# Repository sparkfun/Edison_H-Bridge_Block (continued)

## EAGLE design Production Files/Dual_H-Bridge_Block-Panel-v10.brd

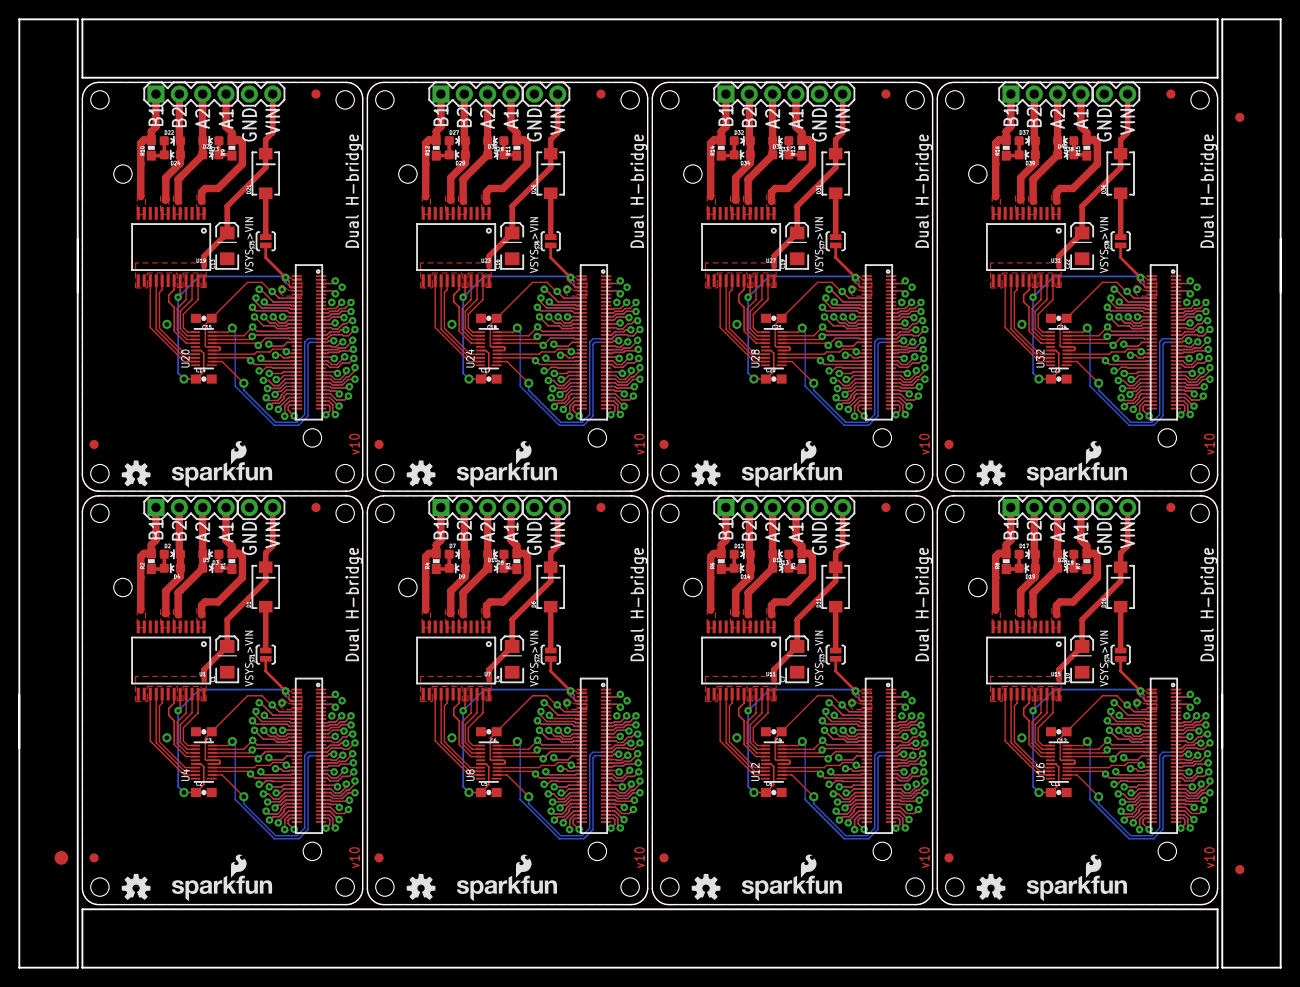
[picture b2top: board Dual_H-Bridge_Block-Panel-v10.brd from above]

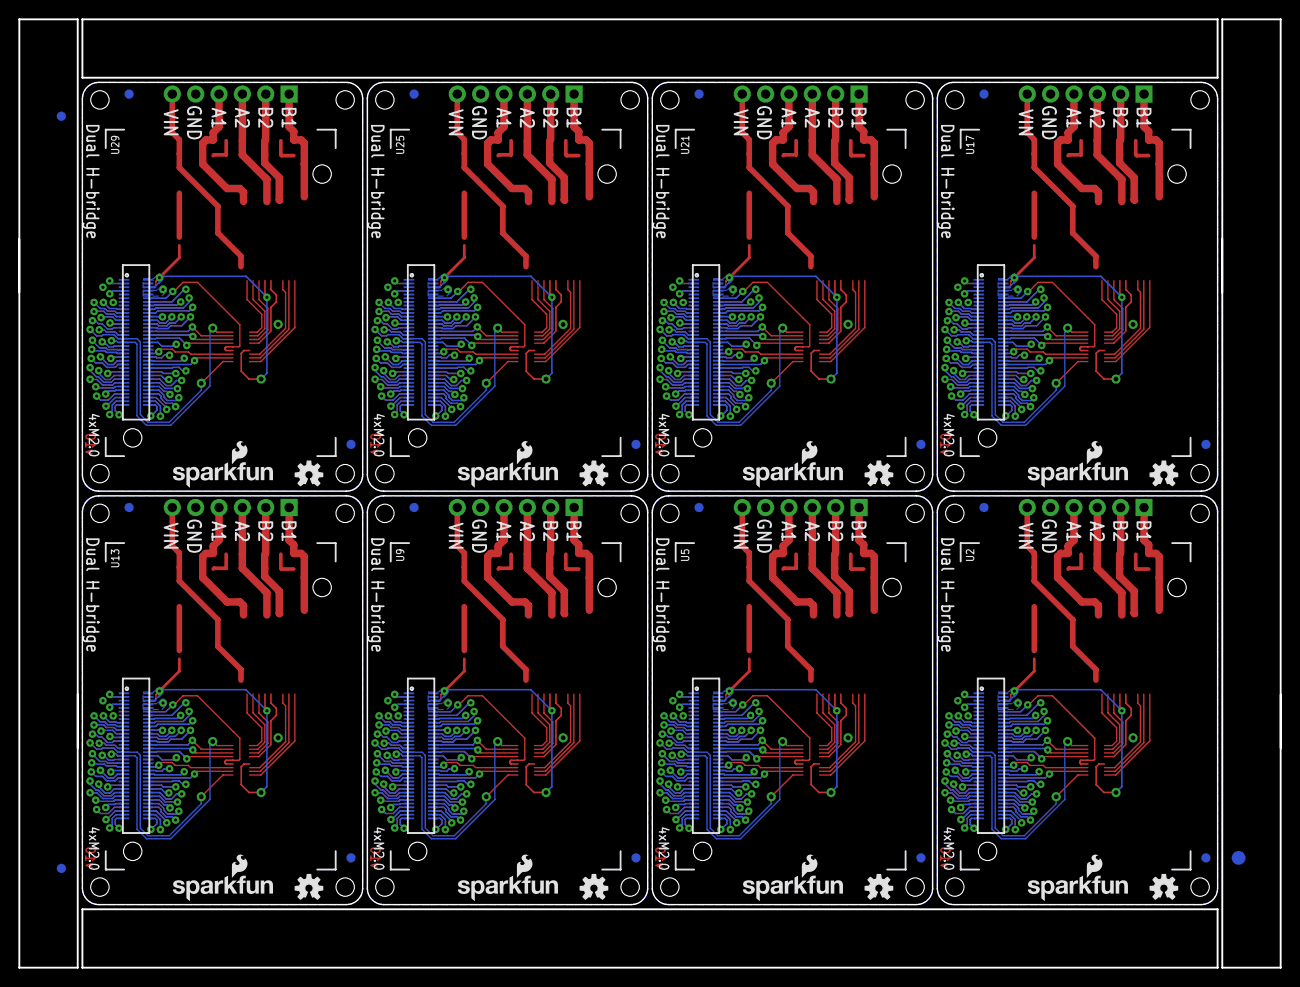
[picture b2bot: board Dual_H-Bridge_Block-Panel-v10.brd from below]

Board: 2 copper layers, 137.2 x 103.1 mm, 206 parts (51 on the bottom side), 584 nets.

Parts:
C1, C4, C7, C10, C13, C16, C19, C22: 10uF; EIA3216
C2, C3, C5, C6, C8, C9, C11, C12, C14, C15, C17, C18, C20, C21, C23, C24: 0.1uF; 0603-CAP
D1, D6, D11, D16, D21, D26, D31, D36: MBRA140; SMA-DIODE
D2, D3, D7, D8, D12, D13, D17, D18, D22, D23, D27, D28, D32, D33, D37, D38: GREEN; LED-0603
D4, D5, D9, D10, D14, D15, D19, D20, D24, D25, D29, D30, D34, D35, D39, D40: RED; LED-0603
E$1, E$2: FIDUCIAL-1.5X3
E$3, E$4, E$5, E$6: FIDUCIAL-1X2
FID1, FID2, FID3, FID4, FID5, FID6, FID7, FID8, FID9, FID10, FID11, FID12, FID13, FID14, FID15, FID16, FID17, FID18, FID19, FID20, FID21, FID22, FID23, FID24, FID25, FID26, FID27, FID28, FID29, FID30, FID31, FID32: FIDUCIAL1X2; FIDUCIAL-1X2
JP1, JP3, JP5, JP7, JP9, JP11, JP13, JP15: 1X04
JP2, JP4, JP6, JP8, JP10, JP12, JP14, JP16: M02PTH; 1X02
LOGO1, LOGO2, LOGO5, LOGO7, LOGO9, LOGO11, LOGO13, LOGO15, LOGO17, LOGO19, LOGO21, LOGO23, LOGO25, LOGO27, LOGO29, LOGO31: OSHW-LOGOS; OSHW-LOGO-S
LOGO3, LOGO4, LOGO6, LOGO8, LOGO10, LOGO12, LOGO14, LOGO16, LOGO18, LOGO20, LOGO22, LOGO24, LOGO26, LOGO28, LOGO30, LOGO32: SFE_LOGO_NAME_FLAME.1_INCH; SFE_LOGO_NAME_FLAME_.1
R1, R2, R3, R4, R5, R6, R7, R8, R9, R10, R11, R12, R13, R14, R15, R16: 680; 0603-RES
SJ1, SJ2, SJ3, SJ4, SJ5, SJ6, SJ7, SJ8: VSYS ENABLE; PAD-JUMPER-2-NO_YES_SILK
U1, U7, U11, U15, U19, U23, U27, U31: TB6612FNG; SSOP24
U2, U5, U9, U13, U17, U21, U25, U29: EDISON_CONNECTOR_FULLMOUNTING_HOLES; EDISON_DAUGHTER
U3, U6, U10, U14, U18, U22, U26, U30: EDISON_CONNECTOR_FULLHEADER; DF40C-70DP-0.4(51)
U4, U8, U12, U16, U20, U24, U28, U32: TXB0108; UFDFN-20

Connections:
1.8V: C3.1, U2.12, U3.12, U4.5, U4.6
1.8V1: C6.1, U5.12, U6.12, U8.5, U8.6
1.8V2: C9.1, U9.12, U10.12, U12.5, U12.6
1.8V3: C12.1, U13.12, U14.12, U16.5, U16.6
1.8V4: C15.1, U17.12, U18.12, U20.5, U20.6
1.8V5: C18.1, U21.12, U22.12, U24.5, U24.6
1.8V6: C21.1, U25.12, U26.12, U28.5, U28.6
1.8V7: C24.1, U29.12, U30.12, U32.5, U32.6
3.3V: U2.8, U2.10, U3.8, U3.10
3.3V1: U5.8, U5.10, U6.8, U6.10
3.3V2: U9.8, U9.10, U10.8, U10.10
3.3V3: U13.8, U13.10, U14.8, U14.10
3.3V4: U17.8, U17.10, U18.8, U18.10
3.3V5: U21.8, U21.10, U22.8, U22.10
3.3V6: U25.8, U25.10, U26.8, U26.10
3.3V7: U29.8, U29.10, U30.8, U30.10
A1: JP1.4, R1.2, U1.1, U1.2
A2: D3.C, D5.A, JP1.3, U1.5, U1.6
A3: D8.C, D10.A, JP3.3, U7.5, U7.6
A4: JP3.4, R3.2, U7.1, U7.2
A5: D13.C, D15.A, JP5.3, U11.5, U11.6
A6: JP5.4, R5.2, U11.1, U11.2
A7: D18.C, D20.A, JP7.3, U15.5, U15.6
A8: JP7.4, R7.2, U15.1, U15.2
A9: D23.C, D25.A, JP9.3, U19.5, U19.6
A10: JP9.4, R9.2, U19.1, U19.2
A11: D28.C, D30.A, JP11.3, U23.5, U23.6
A12: JP11.4, R11.2, U23.1, U23.2
A13: D33.C, D35.A, JP13.3, U27.5, U27.6
A14: JP13.4, R13.2, U27.1, U27.2
A15: D38.C, D40.A, JP15.3, U31.5, U31.6
A16: JP15.4, R15.2, U31.1, U31.2
B1: JP1.1, R2.2, U1.11, U1.12
B2: D2.C, D4.A, JP1.2, U1.7, U1.8
B3: JP3.1, R4.2, U7.11, U7.12
B4: D7.C, D9.A, JP3.2, U7.7, U7.8
B5: JP5.1, R6.2, U11.11, U11.12
B6: D12.C, D14.A, JP5.2, U11.7, U11.8
B7: JP7.1, R8.2, U15.11, U15.12
B8: D17.C, D19.A, JP7.2, U15.7, U15.8
B9: JP9.1, R10.2, U19.11, U19.12
B10: D22.C, D24.A, JP9.2, U19.7, U19.8
B11: JP11.1, R12.2, U23.11, U23.12
B12: D27.C, D29.A, JP11.2, U23.7, U23.8
B13: JP13.1, R14.2, U27.11, U27.12
B14: D32.C, D34.A, JP13.2, U27.7, U27.8
B15: JP15.1, R16.2, U31.11, U31.12
B16: D37.C, D39.A, JP15.2, U31.7, U31.8
DCIN: U2.14, U3.14
DCIN1: U5.14, U6.14
DCIN2: U9.14, U10.14
DCIN3: U13.14, U14.14
DCIN4: U17.14, U18.14
DCIN5: U21.14, U22.14
DCIN6: U25.14, U26.14
DCIN7: U29.14, U30.14
FAULT: U2.19, U3.19
FAULT1: U5.19, U6.19
FAULT2: U9.19, U10.19
FAULT3: U13.19, U14.19
FAULT4: U17.19, U18.19
FAULT5: U21.19, U22.19
FAULT6: U25.19, U26.19
FAULT7: U29.19, U30.19
FW_RCVR: U2.69, U3.69
FW_RCVR1: U5.69, U6.69
FW_RCVR2: U9.69, U10.69
FW_RCVR3: U13.69, U14.69
FW_RCVR4: U17.69, U18.69
FW_RCVR5: U21.69, U22.69
FW_RCVR6: U25.69, U26.69
FW_RCVR7: U29.69, U30.69
GND: C1.C, C2.2, C3.2, JP2.1, U1.3, U1.4, U1.9, U1.10, U1.18, U2.1, U2.5, U2.9, U2.11, U2.13, U2.15, U3.1, U3.5, U3.9, U3.11, U3.13, U3.15, U4.15
GND1: C4.C, C5.2, C6.2, JP4.1, U5.1, U5.5, U5.9, U5.11, U5.13, U5.15, U6.1, U6.5, U6.9, U6.11, U6.13, U6.15, U7.3, U7.4, U7.9, U7.10, U7.18, U8.15
GND2: C7.C, C8.2, C9.2, JP6.1, U9.1, U9.5, U9.9, U9.11, U9.13, U9.15, U10.1, U10.5, U10.9, U10.11, U10.13, U10.15, U11.3, U11.4, U11.9, U11.10, U11.18, U12.15
GND3: C10.C, C11.2, C12.2, JP8.1, U13.1, U13.5, U13.9, U13.11, U13.13, U13.15, U14.1, U14.5, U14.9, U14.11, U14.13, U14.15, U15.3, U15.4, U15.9, U15.10, U15.18, U16.15
GND4: C13.C, C14.2, C15.2, JP10.1, U17.1, U17.5, U17.9, U17.11, U17.13, U17.15, U18.1, U18.5, U18.9, U18.11, U18.13, U18.15, U19.3, U19.4, U19.9, U19.10, U19.18, U20.15
GND5: C16.C, C17.2, C18.2, JP12.1, U21.1, U21.5, U21.9, U21.11, U21.13, U21.15, U22.1, U22.5, U22.9, U22.11, U22.13, U22.15, U23.3, U23.4, U23.9, U23.10, U23.18, U24.15
GND6: C19.C, C20.2, C21.2, JP14.1, U25.1, U25.5, U25.9, U25.11, U25.13, U25.15, U26.1, U26.5, U26.9, U26.11, U26.13, U26.15, U27.3, U27.4, U27.9, U27.10, U27.18, U28.15
GND7: C22.C, C23.2, C24.2, JP16.1, U29.1, U29.5, U29.9, U29.11, U29.13, U29.15, U30.1, U30.5, U30.9, U30.11, U30.13, U30.15, U31.3, U31.4, U31.9, U31.10, U31.18, U32.15
GP1: U5.48, U6.48, U8.3
GP2: U5.42, U6.42, U8.4
GP3: U5.34, U6.34, U8.7
GP4: U5.32, U6.32, U8.8
GP5: U5.30, U6.30, U8.9
GP6: U5.28, U6.28
GP7: U5.26, U6.26
GP8: U5.25, U6.25
GP9: U5.24, U6.24
GP10: U9.48, U10.48, U12.3
GP11: U9.42, U10.42, U12.4
GP12: U9.34, U10.34, U12.7
GP12_PWM0: U2.35, U3.35, U4.10
GP12_PWM1: U5.35, U6.35, U8.10
GP12_PWM2: U9.35, U10.35, U12.10
GP12_PWM3: U13.35, U14.35, U16.10
GP12_PWM4: U17.35, U18.35, U20.10
GP12_PWM5: U21.35, U22.35, U24.10
GP12_PWM6: U25.35, U26.35, U28.10
GP12_PWM7: U29.35, U30.35, U32.10
GP13: U9.32, U10.32, U12.8
GP13_PWM1: U2.33, U3.33, U4.2
GP13_PWM2: U5.33, U6.33, U8.2
GP13_PWM3: U9.33, U10.33, U12.2
GP13_PWM4: U13.33, U14.33, U16.2
GP13_PWM5: U17.33, U18.33, U20.2
GP13_PWM6: U21.33, U22.33, U24.2
GP13_PWM7: U25.33, U26.33, U28.2
GP13_PWM8: U29.33, U30.33, U32.2
GP14: U2.48, U3.48, U4.3
GP15: U2.42, U3.42, U4.4
GP16: U9.30, U10.30, U12.9
GP17: U9.28, U10.28
GP18: U9.26, U10.26
GP19: U9.25, U10.25
GP19_I2C_1_SCL: U2.41, U3.41
GP19_I2C_1_SCL1: U5.41, U6.41
GP19_I2C_1_SCL2: U9.41, U10.41
GP19_I2C_1_SCL3: U13.41, U14.41
GP19_I2C_1_SCL4: U17.41, U18.41
GP19_I2C_1_SCL5: U21.41, U22.41
GP19_I2C_1_SCL6: U25.41, U26.41
GP19_I2C_1_SCL7: U29.41, U30.41
GP20: U9.24, U10.24
GP20_I2C_1_SDA: U2.43, U3.43
GP20_I2C_1_SDA1: U5.43, U6.43
GP20_I2C_1_SDA2: U9.43, U10.43
GP20_I2C_1_SDA3: U13.43, U14.43
GP20_I2C_1_SDA4: U17.43, U18.43
GP20_I2C_1_SDA5: U21.43, U22.43
GP20_I2C_1_SDA6: U25.43, U26.43
GP20_I2C_1_SDA7: U29.43, U30.43
GP21: U13.48, U14.48, U16.3
GP22: U13.42, U14.42, U16.4
GP23: U13.34, U14.34, U16.7
GP24: U13.32, U14.32, U16.8
GP25: U13.30, U14.30, U16.9
GP26: U13.28, U14.28
GP27: U13.26, U14.26
GP27_I2C_6_SCL: U2.45, U3.45
GP27_I2C_6_SCL1: U5.45, U6.45
GP27_I2C_6_SCL2: U9.45, U10.45
GP27_I2C_6_SCL3: U13.45, U14.45
GP27_I2C_6_SCL4: U17.45, U18.45
GP27_I2C_6_SCL5: U21.45, U22.45
GP27_I2C_6_SCL6: U25.45, U26.45
GP27_I2C_6_SCL7: U29.45, U30.45
GP28: U13.25, U14.25
GP28_I2C_6_SDA: U2.47, U3.47
GP28_I2C_6_SDA1: U5.47, U6.47
GP28_I2C_6_SDA2: U9.47, U10.47
GP28_I2C_6_SDA3: U13.47, U14.47
GP28_I2C_6_SDA4: U17.47, U18.47
GP28_I2C_6_SDA5: U21.47, U22.47
GP28_I2C_6_SDA6: U25.47, U26.47
GP28_I2C_6_SDA7: U29.47, U30.47
GP29: U13.24, U14.24
GP30: U17.48, U18.48, U20.3
GP31: U17.42, U18.42, U20.4
GP32: U17.34, U18.34, U20.7
GP33: U17.32, U18.32, U20.8
GP34: U17.30, U18.30, U20.9
GP35: U17.28, U18.28
GP36: U17.26, U18.26
GP37: U17.25, U18.25
GP38: U17.24, U18.24
GP39: U21.48, U22.48, U24.3
GP40: U21.42, U22.42, U24.4
GP40_I2S_2_CLK: U2.52, U3.52
GP40_I2S_2_CLK1: U5.52, U6.52
GP40_I2S_2_CLK2: U9.52, U10.52
GP40_I2S_2_CLK3: U13.52, U14.52
GP40_I2S_2_CLK4: U17.52, U18.52
GP40_I2S_2_CLK5: U21.52, U22.52
GP40_I2S_2_CLK6: U25.52, U26.52
GP40_I2S_2_CLK7: U29.52, U30.52
GP41: U21.34, U22.34, U24.7
GP41_I2S_2_FS: U2.54, U3.54
GP41_I2S_2_FS1: U5.54, U6.54
GP41_I2S_2_FS2: U9.54, U10.54
GP41_I2S_2_FS3: U13.54, U14.54
GP41_I2S_2_FS4: U17.54, U18.54
GP41_I2S_2_FS5: U21.54, U22.54
GP41_I2S_2_FS6: U25.54, U26.54
GP41_I2S_2_FS7: U29.54, U30.54
GP42: U21.32, U22.32, U24.8
GP42_I2S_2_RXD: U2.50, U3.50
GP42_I2S_2_RXD1: U5.50, U6.50
GP42_I2S_2_RXD2: U9.50, U10.50
GP42_I2S_2_RXD3: U13.50, U14.50
GP42_I2S_2_RXD4: U17.50, U18.50
GP42_I2S_2_RXD5: U21.50, U22.50
GP42_I2S_2_RXD6: U25.50, U26.50
GP42_I2S_2_RXD7: U29.50, U30.50
GP43: U21.30, U22.30, U24.9
GP43_I2S_2_TXD: U2.56, U3.56
GP43_I2S_2_TXD1: U5.56, U6.56
GP43_I2S_2_TXD2: U9.56, U10.56
GP43_I2S_2_TXD3: U13.56, U14.56
GP43_I2S_2_TXD4: U17.56, U18.56
GP43_I2S_2_TXD5: U21.56, U22.56
GP43_I2S_2_TXD6: U25.56, U26.56
GP43_I2S_2_TXD7: U29.56, U30.56
GP44: U2.24, U3.24
GP45: U2.26, U3.26
GP46: U2.28, U3.28
GP47: U2.30, U3.30, U4.9
GP48: U2.32, U3.32, U4.8
GP49: U2.34, U3.34, U4.7
GP50: U21.28, U22.28
GP51: U21.26, U22.26
GP52: U21.25, U22.25
GP53: U21.24, U22.24
GP54: U25.48, U26.48, U28.3
GP55: U25.42, U26.42, U28.4
GP56: U25.34, U26.34, U28.7
GP57: U25.32, U26.32, U28.8
GP58: U25.30, U26.30, U28.9
GP59: U25.28, U26.28
GP60: U25.26, U26.26
GP61: U25.25, U26.25
GP62: U25.24, U26.24
GP63: U29.48, U30.48, U32.3
GP64: U29.42, U30.42, U32.4
GP65: U29.34, U30.34, U32.7
GP66: U29.32, U30.32, U32.8
GP67: U29.30, U30.30, U32.9
GP68: U29.28, U30.28
GP69: U29.26, U30.26
GP70: U29.25, U30.25
GP71: U29.24, U30.24
GP77_SD_0_CD#: U2.60, U3.60
GP77_SD_0_CD#1: U5.60, U6.60
GP77_SD_0_CD#2: U9.60, U10.60
GP77_SD_0_CD#3: U13.60, U14.60
GP77_SD_0_CD#4: U17.60, U18.60
GP77_SD_0_CD#5: U21.60, U22.60
GP77_SD_0_CD#6: U25.60, U26.60
GP77_SD_0_CD#7: U29.60, U30.60
GP78_SD_0_CLK: U2.58, U3.58
GP78_SD_0_CLK1: U5.58, U6.58
GP78_SD_0_CLK2: U9.58, U10.58
GP78_SD_0_CLK3: U13.58, U14.58
GP78_SD_0_CLK4: U17.58, U18.58
GP78_SD_0_CLK5: U21.58, U22.58
GP78_SD_0_CLK6: U25.58, U26.58
GP78_SD_0_CLK7: U29.58, U30.58
GP79_SD_0_CMD: U2.62, U3.62
GP79_SD_0_CMD1: U5.62, U6.62
GP79_SD_0_CMD2: U9.62, U10.62
GP79_SD_0_CMD3: U13.62, U14.62
GP79_SD_0_CMD4: U17.62, U18.62
GP79_SD_0_CMD5: U21.62, U22.62
GP79_SD_0_CMD6: U25.62, U26.62
GP79_SD_0_CMD7: U29.62, U30.62
GP80_SD_0_DAT0: U2.66, U3.66
GP80_SD_0_DAT1: U5.66, U6.66
GP80_SD_0_DAT2: U9.66, U10.66
GP80_SD_0_DAT3: U13.66, U14.66
GP80_SD_0_DAT4: U17.66, U18.66
GP80_SD_0_DAT5: U21.66, U22.66
GP80_SD_0_DAT6: U25.66, U26.66
GP80_SD_0_DAT7: U29.66, U30.66
GP81_SD_0_DAT1: U2.70, U3.70
GP81_SD_0_DAT2: U5.70, U6.70
GP81_SD_0_DAT3: U9.70, U10.70
GP81_SD_0_DAT4: U13.70, U14.70
GP81_SD_0_DAT5: U17.70, U18.70
GP81_SD_0_DAT6: U21.70, U22.70
GP81_SD_0_DAT7: U25.70, U26.70
GP81_SD_0_DAT8: U29.70, U30.70
GP82_SD_0_DAT1: U5.64, U6.64
GP82_SD_0_DAT2: U2.64, U3.64
GP82_SD_0_DAT3: U9.64, U10.64
GP82_SD_0_DAT4: U13.64, U14.64
GP82_SD_0_DAT5: U17.64, U18.64
GP82_SD_0_DAT6: U21.64, U22.64
GP82_SD_0_DAT7: U25.64, U26.64
GP82_SD_0_DAT8: U29.64, U30.64
GP83_SD_0_DAT1: U5.68, U6.68
GP83_SD_0_DAT2: U9.68, U10.68
GP83_SD_0_DAT3: U2.68, U3.68
GP83_SD_0_DAT4: U13.68, U14.68
GP83_SD_0_DAT5: U17.68, U18.68
GP83_SD_0_DAT6: U21.68, U22.68
GP83_SD_0_DAT7: U25.68, U26.68
GP83_SD_0_DAT8: U29.68, U30.68
GP84_SD_CLK_FB: U2.44, U3.44
GP84_SD_CLK_FB1: U5.44, U6.44
GP84_SD_CLK_FB2: U9.44, U10.44
GP84_SD_CLK_FB3: U13.44, U14.44
GP84_SD_CLK_FB4: U17.44, U18.44
GP84_SD_CLK_FB5: U21.44, U22.44
GP84_SD_CLK_FB6: U25.44, U26.44
GP84_SD_CLK_FB7: U29.44, U30.44
GP109_SPI_2_CLK: U2.55, U3.55
GP109_SPI_2_CLK1: U5.55, U6.55
GP109_SPI_2_CLK2: U9.55, U10.55
GP109_SPI_2_CLK3: U13.55, U14.55
GP109_SPI_2_CLK4: U17.55, U18.55
GP109_SPI_2_CLK5: U21.55, U22.55
GP109_SPI_2_CLK6: U25.55, U26.55
GP109_SPI_2_CLK7: U29.55, U30.55
GP110_SPI_2_FS0: U2.53, U3.53
GP110_SPI_2_FS1: U5.53, U6.53
GP110_SPI_2_FS2: U9.53, U10.53
GP110_SPI_2_FS3: U13.53, U14.53
GP110_SPI_2_FS4: U17.53, U18.53
GP110_SPI_2_FS5: U21.53, U22.53
GP110_SPI_2_FS6: U25.53, U26.53
GP110_SPI_2_FS7: U29.53, U30.53
GP111_SPI_2_FS1: U2.51, U3.51
GP111_SPI_2_FS2: U5.51, U6.51
GP111_SPI_2_FS3: U9.51, U10.51
GP111_SPI_2_FS4: U13.51, U14.51
GP111_SPI_2_FS5: U17.51, U18.51
GP111_SPI_2_FS6: U21.51, U22.51
GP111_SPI_2_FS7: U25.51, U26.51
GP111_SPI_2_FS8: U29.51, U30.51
GP114_SPI_2_RXD: U2.59, U3.59
GP114_SPI_2_RXD1: U5.59, U6.59
GP114_SPI_2_RXD2: U9.59, U10.59
GP114_SPI_2_RXD3: U13.59, U14.59
GP114_SPI_2_RXD4: U17.59, U18.59
GP114_SPI_2_RXD5: U21.59, U22.59
GP114_SPI_2_RXD6: U25.59, U26.59
GP114_SPI_2_RXD7: U29.59, U30.59
GP115_SPI_2_TXD: U2.57, U3.57
GP115_SPI_2_TXD1: U5.57, U6.57
GP115_SPI_2_TXD2: U9.57, U10.57
GP115_SPI_2_TXD3: U13.57, U14.57
GP115_SPI_2_TXD4: U17.57, U18.57
GP115_SPI_2_TXD5: U21.57, U22.57
GP115_SPI_2_TXD6: U25.57, U26.57
GP115_SPI_2_TXD7: U29.57, U30.57
GP128_UART_1_CTS: U2.65, U3.65
GP128_UART_1_CTS1: U5.65, U6.65
GP128_UART_1_CTS2: U9.65, U10.65
GP128_UART_1_CTS3: U13.65, U14.65
GP128_UART_1_CTS4: U17.65, U18.65
GP128_UART_1_CTS5: U21.65, U22.65
GP128_UART_1_CTS6: U25.65, U26.65
GP128_UART_1_CTS7: U29.65, U30.65
GP129_UART_1_RTS: U2.63, U3.63
GP129_UART_1_RTS1: U5.63, U6.63
GP129_UART_1_RTS2: U9.63, U10.63
GP129_UART_1_RTS3: U13.63, U14.63
GP129_UART_1_RTS4: U17.63, U18.63
GP129_UART_1_RTS5: U21.63, U22.63
GP129_UART_1_RTS6: U25.63, U26.63
GP129_UART_1_RTS7: U29.63, U30.63
GP130_UART_1_RX: U2.61, U3.61
GP130_UART_1_RX1: U5.61, U6.61
GP130_UART_1_RX2: U9.61, U10.61
GP130_UART_1_RX3: U13.61, U14.61
GP130_UART_1_RX4: U17.61, U18.61
GP130_UART_1_RX5: U21.61, U22.61
GP130_UART_1_RX6: U25.61, U26.61
GP130_UART_1_RX7: U29.61, U30.61
GP131_UART_1_TX: U2.46, U3.46
GP131_UART_1_TX1: U5.46, U6.46
GP131_UART_1_TX2: U9.46, U10.46
GP131_UART_1_TX3: U13.46, U14.46
GP131_UART_1_TX4: U17.46, U18.46
GP131_UART_1_TX5: U21.46, U22.46
GP131_UART_1_TX6: U25.46, U26.46
GP131_UART_1_TX7: U29.46, U30.46
GP134_UART_2_RX: U2.22, U3.22
GP134_UART_2_RX1: U5.22, U6.22
GP134_UART_2_RX2: U9.22, U10.22
GP134_UART_2_RX3: U13.22, U14.22
GP134_UART_2_RX4: U17.22, U18.22
GP134_UART_2_RX5: U21.22, U22.22
GP134_UART_2_RX6: U25.22, U26.22
GP134_UART_2_RX7: U29.22, U30.22
GP135_UART_2_TX: U2.27, U3.27
GP135_UART_2_TX1: U5.27, U6.27
GP135_UART_2_TX2: U9.27, U10.27
GP135_UART_2_TX3: U13.27, U14.27
GP135_UART_2_TX4: U17.27, U18.27
GP135_UART_2_TX5: U21.27, U22.27
GP135_UART_2_TX6: U25.27, U26.27
GP135_UART_2_TX7: U29.27, U30.27
GP165: U2.25, U3.25
GP182_PWM1: U5.37, U6.37
GP182_PWM2: U2.37, U3.37
GP182_PWM3: U9.37, U10.37
GP182_PWM4: U13.37, U14.37
GP182_PWM5: U17.37, U18.37
GP182_PWM6: U21.37, U22.37
GP182_PWM7: U25.37, U26.37
GP182_PWM8: U29.37, U30.37
GP183_PWM1: U5.39, U6.39
GP183_PWM2: U9.39, U10.39
GP183_PWM3: U2.39, U3.39
GP183_PWM4: U13.39, U14.39
GP183_PWM5: U17.39, U18.39
GP183_PWM6: U21.39, U22.39
GP183_PWM7: U25.39, U26.39
GP183_PWM8: U29.39, U30.39
MSIC_SLP_CLK: U2.7, U3.7
MSIC_SLP_CLK1: U5.7, U6.7
MSIC_SLP_CLK2: U9.7, U10.7
MSIC_SLP_CLK3: U13.7, U14.7
MSIC_SLP_CLK4: U17.7, U18.7
MSIC_SLP_CLK5: U21.7, U22.7
MSIC_SLP_CLK6: U25.7, U26.7
MSIC_SLP_CLK7: U29.7, U30.7
unnamed: D1.A, SJ1.2
unnamed: D2.A, D4.C, R2.1
unnamed: U1.15, U4.19
unnamed: U1.23, U4.11
unnamed: D3.A, D5.C, R1.1
unnamed: U7.19, U8.14
unnamed: U7.17, U8.17
unnamed: U7.16, U8.18
unnamed: U7.21, U8.13
unnamed: U1.19, U4.14
unnamed: U1.17, U4.17
unnamed: U1.16, U4.18
unnamed: U7.22, U8.12
unnamed: U1.21, U4.13
unnamed: U1.22, U4.12
unnamed: U7.15, U8.19
unnamed: U7.23, U8.11
unnamed: D6.A, SJ2.2
unnamed: D7.A, D9.C, R4.1
unnamed: D8.A, D10.C, R3.1
unnamed: U11.19, U12.14
unnamed: U11.17, U12.17
unnamed: U11.16, U12.18
unnamed: U11.21, U12.13
unnamed: U11.22, U12.12
unnamed: U11.15, U12.19
unnamed: U11.23, U12.11
unnamed: D11.A, SJ3.2
unnamed: D12.A, D14.C, R6.1
unnamed: D13.A, D15.C, R5.1
unnamed: U15.19, U16.14
unnamed: U15.17, U16.17
unnamed: U15.16, U16.18
unnamed: U15.21, U16.13
unnamed: U15.22, U16.12
unnamed: U15.15, U16.19
unnamed: U15.23, U16.11
unnamed: D16.A, SJ4.2
unnamed: D17.A, D19.C, R8.1
unnamed: D18.A, D20.C, R7.1
unnamed: U19.19, U20.14
unnamed: U19.17, U20.17
unnamed: U19.16, U20.18
unnamed: U19.21, U20.13
unnamed: U19.22, U20.12
unnamed: U19.15, U20.19
unnamed: U19.23, U20.11
unnamed: D21.A, SJ5.2
unnamed: D22.A, D24.C, R10.1
unnamed: D23.A, D25.C, R9.1
unnamed: U23.19, U24.14
unnamed: U23.17, U24.17
unnamed: U23.16, U24.18
unnamed: U23.21, U24.13
unnamed: U23.22, U24.12
unnamed: U23.15, U24.19
unnamed: U23.23, U24.11
unnamed: D26.A, SJ6.2
unnamed: D27.A, D29.C, R12.1
unnamed: D28.A, D30.C, R11.1
unnamed: U27.19, U28.14
unnamed: U27.17, U28.17
unnamed: U27.16, U28.18
unnamed: U27.21, U28.13
unnamed: U27.22, U28.12
unnamed: U27.15, U28.19
unnamed: U27.23, U28.11
unnamed: D31.A, SJ7.2
unnamed: D32.A, D34.C, R14.1
unnamed: D33.A, D35.C, R13.1
unnamed: U31.19, U32.14
unnamed: U31.17, U32.17
unnamed: U31.16, U32.18
unnamed: U31.21, U32.13
unnamed: U31.22, U32.12
unnamed: U31.15, U32.19
unnamed: U31.23, U32.11
unnamed: D36.A, SJ8.2
unnamed: D37.A, D39.C, R16.1
unnamed: D38.A, D40.C, R15.1
OSC_CLK_OUT: U2.67, U3.67
OSC_CLK_OUT1: U5.67, U6.67
OSC_CLK_OUT2: U9.67, U10.67
OSC_CLK_OUT3: U13.67, U14.67
OSC_CLK_OUT4: U17.67, U18.67
OSC_CLK_OUT5: U21.67, U22.67
OSC_CLK_OUT6: U25.67, U26.67
OSC_CLK_OUT7: U29.67, U30.67
PSW: U2.21, U3.21
PSW1: U5.21, U6.21
PSW2: U9.21, U10.21
PSW3: U13.21, U14.21
PSW4: U17.21, U18.21
PSW5: U21.21, U22.21
PSW6: U25.21, U26.21
PSW7: U29.21, U30.21
PWRBTN#: U2.17, U3.17
PWRBTN#1: U5.17, U6.17
PWRBTN#2: U9.17, U10.17
PWRBTN#3: U13.17, U14.17
PWRBTN#4: U17.17, U18.17
PWRBTN#5: U21.17, U22.17
PWRBTN#6: U25.17, U26.17
PWRBTN#7: U29.17, U30.17
RCVR_MODE: U2.31, U3.31
RCVR_MODE1: U5.31, U6.31
RCVR_MODE2: U9.31, U10.31
RCVR_MODE3: U13.31, U14.31
RCVR_MODE4: U17.31, U18.31
RCVR_MODE5: U21.31, U22.31
RCVR_MODE6: U25.31, U26.31
RCVR_MODE7: U29.31, U30.31
RESET_OUT#: U2.36, U3.36
RESET_OUT#1: U5.36, U6.36
RESET_OUT#2: U9.36, U10.36
RESET_OUT#3: U13.36, U14.36
RESET_OUT#4: U17.36, U18.36
RESET_OUT#5: U21.36, U22.36
RESET_OUT#6: U25.36, U26.36
RESET_OUT#7: U29.36, U30.36
USB_DN: U2.18, U3.18
USB_DN1: U5.18, U6.18
USB_DN2: U9.18, U10.18
USB_DN3: U13.18, U14.18
USB_DN4: U17.18, U18.18
USB_DN5: U21.18, U22.18
USB_DN6: U25.18, U26.18
USB_DN7: U29.18, U30.18
USB_DP: U2.16, U3.16
USB_DP1: U5.16, U6.16
USB_DP2: U9.16, U10.16
USB_DP3: U13.16, U14.16
USB_DP4: U17.16, U18.16
USB_DP5: U21.16, U22.16
USB_DP6: U25.16, U26.16
USB_DP7: U29.16, U30.16
USB_ID: U2.3, U3.3
USB_ID1: U5.3, U6.3
USB_ID2: U9.3, U10.3
USB_ID3: U13.3, U14.3
USB_ID4: U17.3, U18.3
USB_ID5: U21.3, U22.3
USB_ID6: U25.3, U26.3
USB_ID7: U29.3, U30.3
USB_VBUS: U2.20, U3.20
USB_VBUS1: U5.20, U6.20
USB_VBUS2: U9.20, U10.20
USB_VBUS3: U13.20, U14.20
USB_VBUS4: U17.20, U18.20
USB_VBUS5: U21.20, U22.20
USB_VBUS6: U25.20, U26.20
USB_VBUS7: U29.20, U30.20
VIN: C1.A, D1.C, JP2.2, U1.13, U1.14, U1.24
VIN1: C4.A, D6.C, JP4.2, U7.13, U7.14, U7.24
VIN2: C7.A, D11.C, JP6.2, U11.13, U11.14, U11.24
VIN3: C10.A, D16.C, JP8.2, U15.13, U15.14, U15.24
VIN4: C13.A, D21.C, JP10.2, U19.13, U19.14, U19.24
VIN5: C16.A, D26.C, JP12.2, U23.13, U23.14, U23.24
VIN6: C19.A, D31.C, JP14.2, U27.13, U27.14, U27.24
VIN7: C22.A, D36.C, JP16.2, U31.13, U31.14, U31.24
VSYS: C2.1, SJ1.1, U1.20, U2.2, U2.4, U2.6, U3.2, U3.4, U3.6, U4.16
VSYS1: C5.1, SJ2.1, U5.2, U5.4, U5.6, U6.2, U6.4, U6.6, U7.20, U8.16
VSYS2: C8.1, SJ3.1, U9.2, U9.4, U9.6, U10.2, U10.4, U10.6, U11.20, U12.16
VSYS3: C11.1, SJ4.1, U13.2, U13.4, U13.6, U14.2, U14.4, U14.6, U15.20, U16.16
VSYS4: C14.1, SJ5.1, U17.2, U17.4, U17.6, U18.2, U18.4, U18.6, U19.20, U20.16
VSYS5: C17.1, SJ6.1, U21.2, U21.4, U21.6, U22.2, U22.4, U22.6, U23.20, U24.16
VSYS6: C20.1, SJ7.1, U25.2, U25.4, U25.6, U26.2, U26.4, U26.6, U27.20, U28.16
VSYS7: C23.1, SJ8.1, U29.2, U29.4, U29.6, U30.2, U30.4, U30.6, U31.20, U32.16
V_BAT_BKUP: U2.23, U3.23
V_BAT_BKUP1: U5.23, U6.23
V_BAT_BKUP2: U9.23, U10.23
V_BAT_BKUP3: U13.23, U14.23
V_BAT_BKUP4: U17.23, U18.23
V_BAT_BKUP5: U21.23, U22.23
V_BAT_BKUP6: U25.23, U26.23
V_BAT_BKUP7: U29.23, U30.23
